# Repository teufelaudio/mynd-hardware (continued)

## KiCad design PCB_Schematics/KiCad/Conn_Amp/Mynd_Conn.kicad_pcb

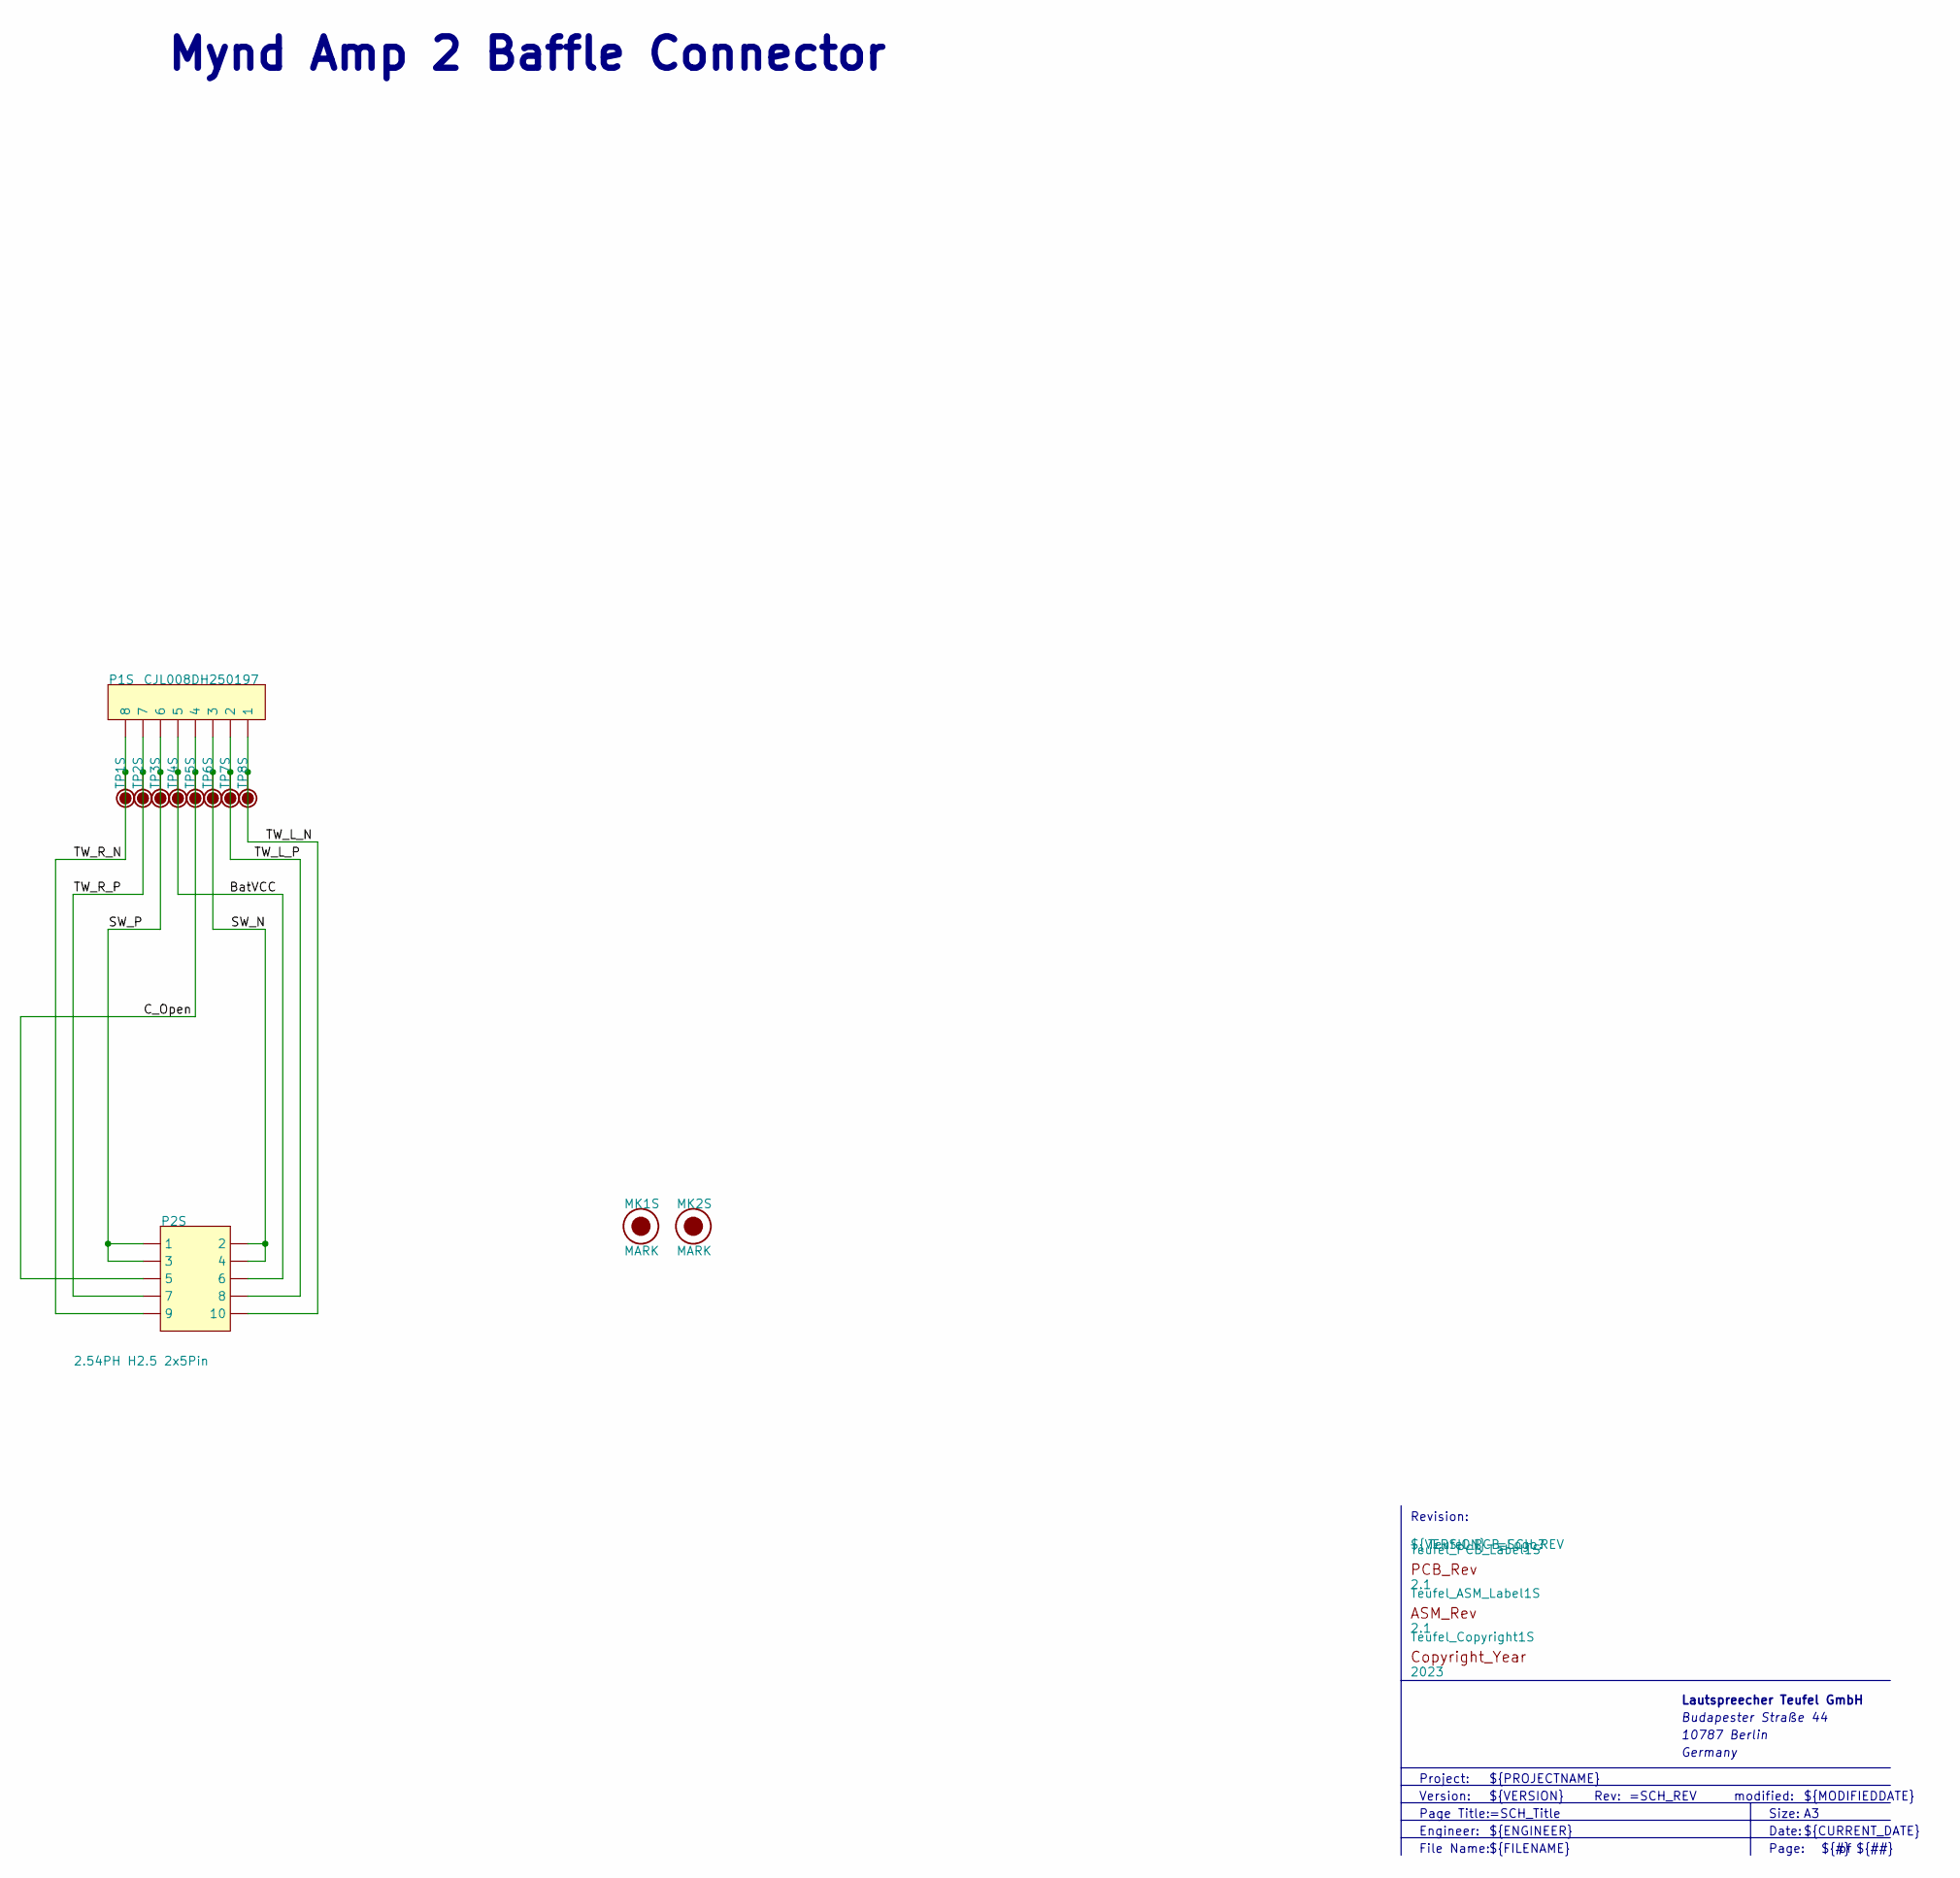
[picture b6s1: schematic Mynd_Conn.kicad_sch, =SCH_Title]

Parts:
MK1S, MK2S: MARK
P1S: CJL008DH250197; PART_NUMBER CJL008DH250197
P2S: 2.54PH H2.5 2x5Pin; Pin_Header_SMD_Side_2X5_254; PART_NUMBER 2.54PH H2.5 2x5Pin
TP1S, TP2S, TP3S, TP4S, TP5S, TP6S, TP7S, TP8S: TP12; TP120
Teufel_ASM_Label1S: 2.1; Teufel_ASM_Rev
Teufel_Copyright1S: 2023; Teufel_Copyright
Teufel_PCB_Label1S: 2.1; Teufel_PCB_Rev

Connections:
BatVCC: P1S.5, P2S.6, TP4S.1
C_Open: P1S.4, P2S.5, TP5S.1
SW_N: P1S.3, P2S.2, P2S.4, TP6S.1
SW_P: P1S.6, P2S.1, P2S.3, TP3S.1
TW_L_N: P1S.1, P2S.10, TP8S.1
TW_L_P: P1S.2, P2S.8, TP7S.1
TW_R_N: P1S.8, P2S.9, TP1S.1
TW_R_P: P1S.7, P2S.7, TP2S.1

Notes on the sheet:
Mynd Amp 2 Baffle Connector
${FILENAME}
Date:
Version:
Germany
Size:
Page Title:
${PROJECTNAME}
Lautspreecher Teufel GmbH
modified:
Budapester Straße 44
${REVISION}
${MODIFIEDDATE}
Revision:
Project:
${#}
Rev:
${ENGINEER}
File Name:
${CURRENT_DATE}
${VERSION}
Page:
${##}
Engineer:
${TITLE}
10787 Berlin

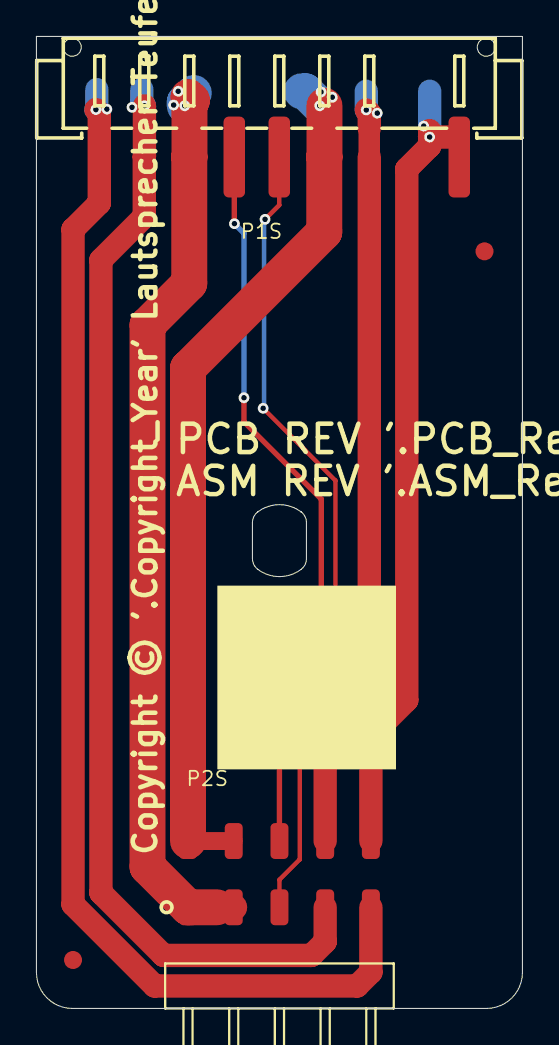
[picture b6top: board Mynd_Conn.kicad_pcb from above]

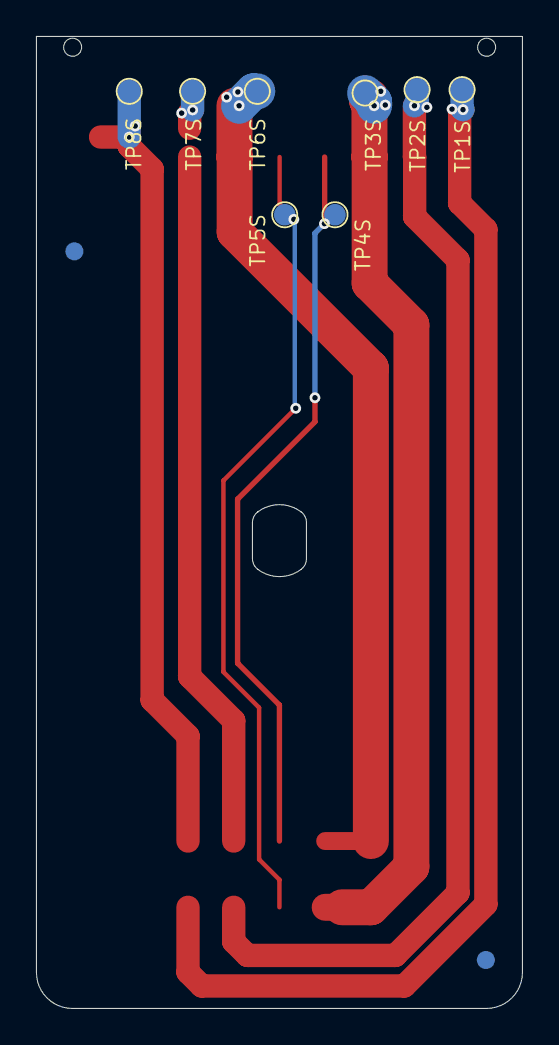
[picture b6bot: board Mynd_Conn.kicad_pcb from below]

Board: 2 copper layers, 27.0 x 54.0 mm, 16 parts (8 on the bottom side), 8 nets.

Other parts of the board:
Teufel_PCB_Logo?: T.3.0.0040-2.1; Teufel_NoLogo

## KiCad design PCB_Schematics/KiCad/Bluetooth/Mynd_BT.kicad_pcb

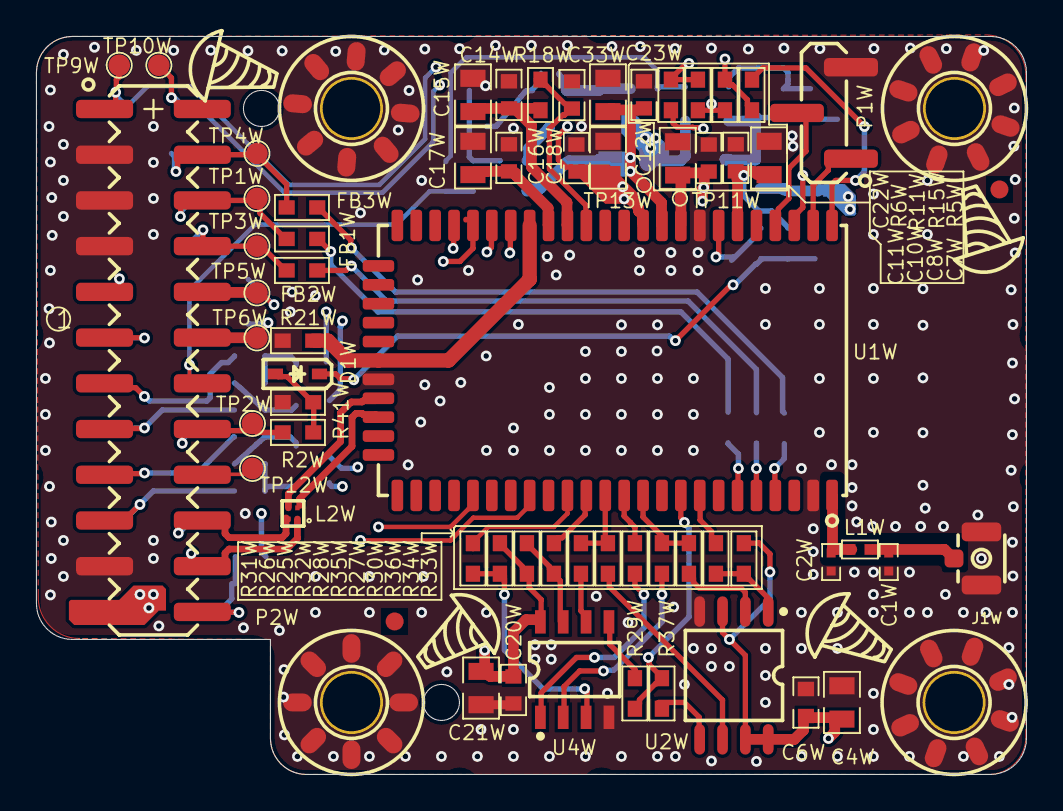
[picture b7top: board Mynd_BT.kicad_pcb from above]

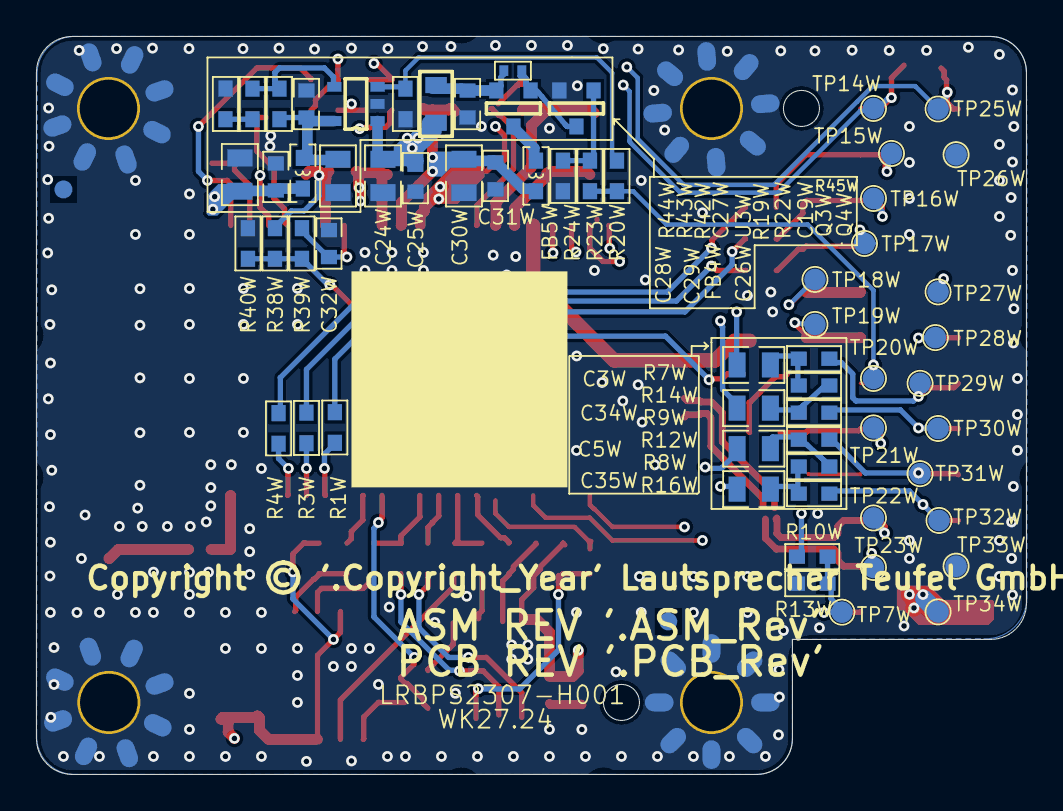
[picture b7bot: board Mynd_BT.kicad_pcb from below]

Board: 4 copper layers, 55.0 x 41.0 mm, 136 parts (66 on the bottom side), 79 nets.

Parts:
C1W, C2W: 0.5pF; C0402
C3W, C4W, C5W, C7W, C11W, C12W, C15W, C17W, C21W, C23W, C24W, C26W, C28W, C30W, C34W, C35W: 10uF; C0805_145
C6W, C8W, C10W, C14W, C16W, C18W, C19W, C20W, C22W, C25W, C27W, C29W, C31W: 100nF; C0603X100
C32W: 100pF; C0603X80
C33W: 1nF; C0603X100
D1W: 1N4148; SOD-323
FB1W, FB2W, FB3W: 0R; R0603
FB4W, FB5W: 600R; L0603
J1W: 9181-000030; I-PEX MHF
L1W: 0R; R0402
L2W: 90R; COM_CHOKE_SMD_ICMF062P
MH1W, MH2W, MH3W, MH4W: SCREW_HOLE; SCREW_D32
MK1W, MK2W: MARK
P1W: Header 3P PITCH=2.54mm SMT; Pin_Header_SMD_S_T_254_3P
P2W: Connector 2 x 12P 2.54mm SMT; Pin_Header_SMD_2X12_254
Q3W: CJ3401; SOT23-GSD
Q4W: 2N7002K; SOT23-GSD
R1W, R3W, R4W, R27W, R28W, R29W, R30W, R31W, R32W, R34W, R35W, R36W, R37W: 33R; R0603
R2W, R11W, R13W, R15W, R25W, R26W, R33W: 10k; R0603
R5W, R6W, R9W, R16W, R21W: 0R; R0603
R7W, R12W: 3.3k; R0603
R8W, R14W: 6.8k; R0603
R10W: 100k; R0603
R18W: 33k; R0603
R19W, R24W, R41W: 47k; R0603
R20W, R23W, R39W: 1k; R0603
R22W: 2.2R; R0805
R38W: 1M; R0603
R40W: 560k; R0603
R42W: 680k; R0603
R43W: 150k; R0603
R44W: 20k; R0603
R45W: 100k; R0402
TP1W, TP2W, TP3W, TP4W, TP5W, TP6W, TP7W, TP9W, TP10W, TP12W, TP14W, TP15W, TP16W, TP17W, TP18W, TP19W, TP20W, TP21W, TP22W, TP23W, TP25W, TP26W, TP27W, TP28W, TP29W, TP30W, TP31W, TP32W, TP33W, TP34W: TP12; TP120
TP11W, TP13W: TP06; TP060
Teufel_ASM_Label1W: =Comment/Name; Teufel_ASM_Rev
Teufel_Copyright1W: =Comment/Name; TEUFEL_COPYRIGHT
Teufel_PCB_Label1W: =Comment/Name; Teufel_PCB_Rev
Teufel_PCB_Logo1W: T.3.0.0040-3.1; Teufel_NoLogo
U1W: WB-2835P; BT_59P_L260XW150XH26_P105
U2W: RCI025064-B000; SO_8_200
U3W: SGM2036-ADJYN5G/TR; SOT23-5
U4W: APS6404L-3SQN; SO-8

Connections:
3V3_STB: P2W.11, R10W.1, TP28W.1
5V_CCPD: C24W.1, C25W.2, P2W.23, R22W.2, TP34W.1, U3W.1
AGND: R21W.2, U1W.30, U1W.43
BT_2_BCLK: FB1W.1, P2W.6, TP1W.1, TP16W.1
BT_2_LRCK: FB2W.1, P2W.8, TP3W.1, TP17W.1
BT_2_SDAT: FB3W.1, P2W.4, TP4W.1, TP15W.1
BT_AVCC: C16W.1, C17W.2, U1W.44
BT_Ctrl_Pwr: P2W.14, R20W.2, R23W.1, TP20W.1
BT_Ctrl_Vreg: P2W.18, TP12W.1
BT_RTCVDD: C7W.1, C8W.1, R38W.1, U1W.54
BT_SCL: P2W.2, R5W.1, R15W.2, TP10W.1, TP14W.1
BT_SDA: P2W.1, R6W.1, R11W.2, TP9W.1, TP25W.1
BT_SVCC: C14W.1, C15W.2, R18W.1, U1W.45
BT_VBAT: C10W.2, C11W.2, C28W.1, C29W.2, FB4W.2, TP11W.1, U1W.51
BT_VBUS: C22W.1, C23W.1, C30W.2, C31W.2, FB5W.2, TP13W.1, U1W.50
BT_VCC: C4W.2, C6W.2, C12W.2, C18W.2, C20W.1, C21W.1, R11W.1, R15W.1, R25W.1, R26W.1, R33W.1, U1W.49, U2W.3, U2W.7, U2W.8, U4W.8
BT_Ver: P2W.24, R10W.2, R13W.1, TP7W.1
BUD_N: L2W.4, U1W.28
BUD_P: L2W.3, U1W.27
FLASH_CS: R33W.2, R34W.2, U2W.1
FLASH_MISO: R36W.2, U2W.2
FLASH_MOSI: R37W.2, U2W.5
FLASH_SCLK: R35W.2, U2W.6
GND: C1W.2, C2W.2, C4W.1, C6W.1, C7W.2, C8W.2, C10W.1, C11W.1, C12W.1, C14W.2, C15W.1, C16W.2, C17W.1, C18W.1, C19W.2, C20W.2, C21W.2, C22W.2, C23W.2, C24W.2, C25W.1, C26W.2, C27W.1, C28W.2, C29W.1, C30W.1, C31W.1, C32W.1, C33W.1, J1W.2, MH1W.1, MH2W.1, MH3W.1, MH4W.1, P1W.3, P2W.3, P2W.5, P2W.7, P2W.21, Q4W.S, R13W.2, R19W.2, R21W.1, R24W.2, R40W.2, R41W.2, R44W.1, TP26W.1, TP33W.1, U1W.2, U1W.29, U1W.52, U2W.4, U3W.2, U4W.4
GPIO0: R5W.2, U1W.59
GPIO1: R6W.2, U1W.57
GPIO2/UART_RX: P1W.1, U1W.58
GPIO3/UART_TX: P1W.2, U1W.56
GPIO8: R27W.1, U1W.12
GPIO9: R28W.1, R35W.1, U1W.13
GPIO10: R30W.1, R36W.1, U1W.11
GPIO11: R29W.1, R37W.1, U1W.9
GPIO13: R32W.1, U1W.14
GPIO14: R31W.1, U1W.15
GPIO16: R34W.1, U1W.8
Line_L_N: P2W.15, R9W.2, TP30W.1
Line_L_P: P2W.13, R7W.2, TP29W.1
Line_R_N: P2W.19, R16W.2, TP32W.1
Line_R_P: P2W.17, R12W.2, TP31W.1
MCU_RX: P2W.10, TP5W.1, TP18W.1, U1W.20
MCU_TX: P2W.12, TP6W.1, TP19W.1, U1W.17
NetC1W_1: C1W.1, J1W.1, L1W.1
NetC2W_1: C2W.1, L1W.2, U1W.1
NetC3W_1: C3W.1, U1W.39
NetC3W_2: C3W.2, R7W.1, R14W.2
NetC5W_1: C5W.1, U1W.41
NetC5W_2: C5W.2, R8W.2, R12W.1
NetC19W_1: C19W.1, Q3W.S, R22W.1, R45W.1
NetC26W_1: C26W.1, C27W.2, FB4W.1, R42W.1, U3W.5
NetC32W_2: C32W.2, R39W.2, U1W.53
NetC33W_2: C33W.2, R18W.2, U1W.46
NetC34W_1: C34W.1, U1W.40
NetC34W_2: C34W.2, R9W.1, R14W.1
NetC35W_1: C35W.1, U1W.42
NetC35W_2: C35W.2, R8W.1, R16W.1
NetD1W_A: D1W.A, R2W.1, R41W.1
NetFB1W_2: FB1W.2, R1W.2
NetFB2W_2: FB2W.2, R3W.2
NetFB3W_2: FB3W.2, R4W.2
NetFB5W_1: FB5W.1, Q3W.D
NetQ3W_G: Q3W.G, Q4W.D, R45W.2
NetQ4W_G: Q4W.G, R23W.2, R24W.1
NetR1W_1: R1W.1, U1W.6
NetR3W_1: R3W.1, U1W.5
NetR4W_1: R4W.1, U1W.4
NetR19W_1: R19W.1, R20W.1, U3W.3
NetR42W_2: R42W.2, R43W.2, U3W.4
NetR43W_1: R43W.1, R44W.2
ON/OFF: D1W.K, R38W.2, R39W.1, R40W.1
PSRAM_CE: R27W.2, U4W.1
PSRAM_SCLK: R28W.2, U4W.6
PSRAM_SIO0: R29W.2, U4W.5
PSRAM_SIO1: R30W.2, U4W.2
PSRAM_SIO2: R26W.2, R31W.2, U4W.3
PSRAM_SIO3: R25W.2, R32W.2, U4W.7
USB_B_N: L2W.2, P2W.20, TP22W.1
USB_B_P: L2W.1, P2W.22, TP23W.1
VSys: P2W.9, TP27W.1
\BT_RST: P2W.16, R2W.2, TP2W.1, TP21W.1

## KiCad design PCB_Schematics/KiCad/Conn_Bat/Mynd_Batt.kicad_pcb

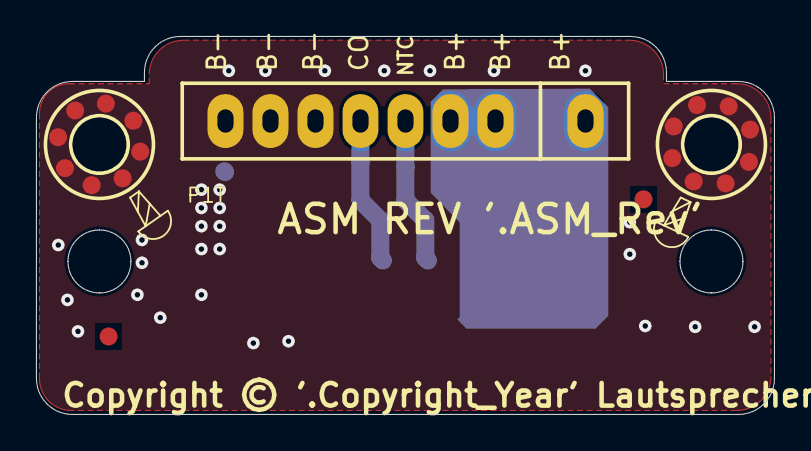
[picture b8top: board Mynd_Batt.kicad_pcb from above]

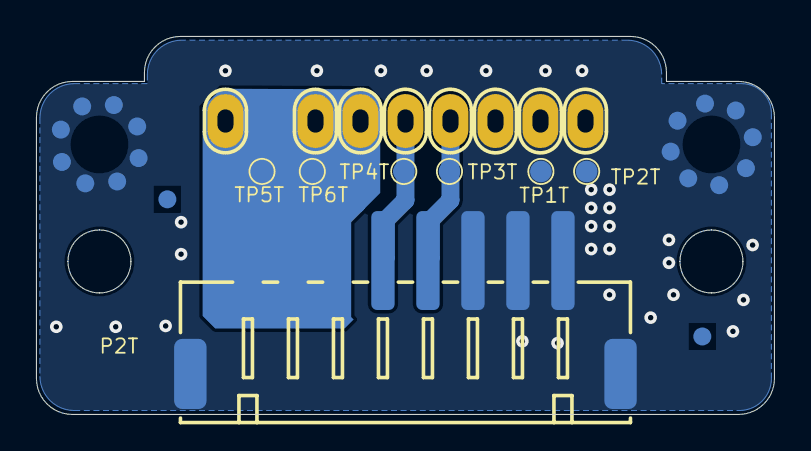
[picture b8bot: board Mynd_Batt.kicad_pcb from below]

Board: 2 copper layers, 41.0 x 21.0 mm, 15 parts (7 on the bottom side), 4 nets.

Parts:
MH1T, MH2T: SCREW_HOLE; SCREW_D30
MK1T, MK2T: MARK
P1T: 8P PITCH=2.5mm; TSB1_05282
P2T: WT250MW-084R-0W; CON_250_SMD_H_8P
TP1T, TP2T, TP3T, TP4T, TP5T, TP6T: TP12; TP120
Teufel_ASM_Label1T: 3.1; Teufel_ASM_Rev
Teufel_Copyright1T: 2023; TEUFEL_COPYRIGHT
Teufel_PCB_Logo1T: Teufel_NoLogo

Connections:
Bat+: P1T.1, P1T.2, P1T.3, P2T.6, P2T.7, P2T.8, TP5T.1, TP6T.1
Bat-: MH1T.1, MH2T.1, P1T.6, P1T.7, P1T.8, P2T.0, P2T.1, P2T.2, P2T.3, TP1T.1, TP2T.1
C_Open: P1T.5, P2T.4, TP3T.1
NTC: P1T.4, P2T.5, TP4T.1

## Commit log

2026-03-19 Added MYNDberry PCB/Schematic and Production Files
